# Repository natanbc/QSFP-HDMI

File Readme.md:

# QSFP to HDMI Breakout Boards

This repository contains two KiCad subprojects for the QSFP to HDMI breakout boards. These subprojects are designed to facilitate the conversion of QSFP signals to HDMI.

The concept has been created to be used on the Microsoft Stratix V FPGA accelerator card "Storey Peak". Jan Marjanovic has created a series of posts about the analysis of the card:

- [Part 1](https://j-marjanovic.io/stratix-v-accelerator-card-from-ebay.html)
- [Part 2](https://j-marjanovic.io/stratix-v-accelerator-card-from-ebay-part-2.html)
- [Part 3](https://j-marjanovic.io/stratix-v-accelerator-card-from-ebay-part-3.html)
- [Part 4](https://j-marjanovic.io/stratix-v-accelerator-card-from-ebay-part-4.html)
- [Part 5](https://j-marjanovic.io/stratix-v-accelerator-card-from-ebay-part-5.html)
- [Part 6](https://j-marjanovic.io/stratix-v-accelerator-card-from-ebay-part-6.html)
- [Part 7](https://j-marjanovic.io/stratix-v-accelerator-card-from-ebay-part-7.html)
- [Part 8](https://j-marjanovic.io/stratix-v-accelerator-card-from-ebay-part-8.html)

## Subprojects

### 1. QSFP breakout board

The project is just a breakout board for the QSFP connector allowing connection to the QSFP on the FPGA board.

### 2. QSFP to HDMI and UART Adapter

This subproject focuses on the design and implementation of an adapter that converts QSFP signals to HDMI. The key features include:

- QSFP connector for input signals
- HDMI connector for output signals
- USB-C connector for UART adapter

This board has been manufactured in JLCPCB, and has LCSC part numbers allowing assembly by them as well. Be sure to use 1mm PCBs to fit into the QSFP slot.

## Contributing

Contributions are welcome! Please fork the repository and submit a pull request with your improvements.

## License

This project is licensed under the MIT License. See the [LICENSE](LICENSE) file for details.

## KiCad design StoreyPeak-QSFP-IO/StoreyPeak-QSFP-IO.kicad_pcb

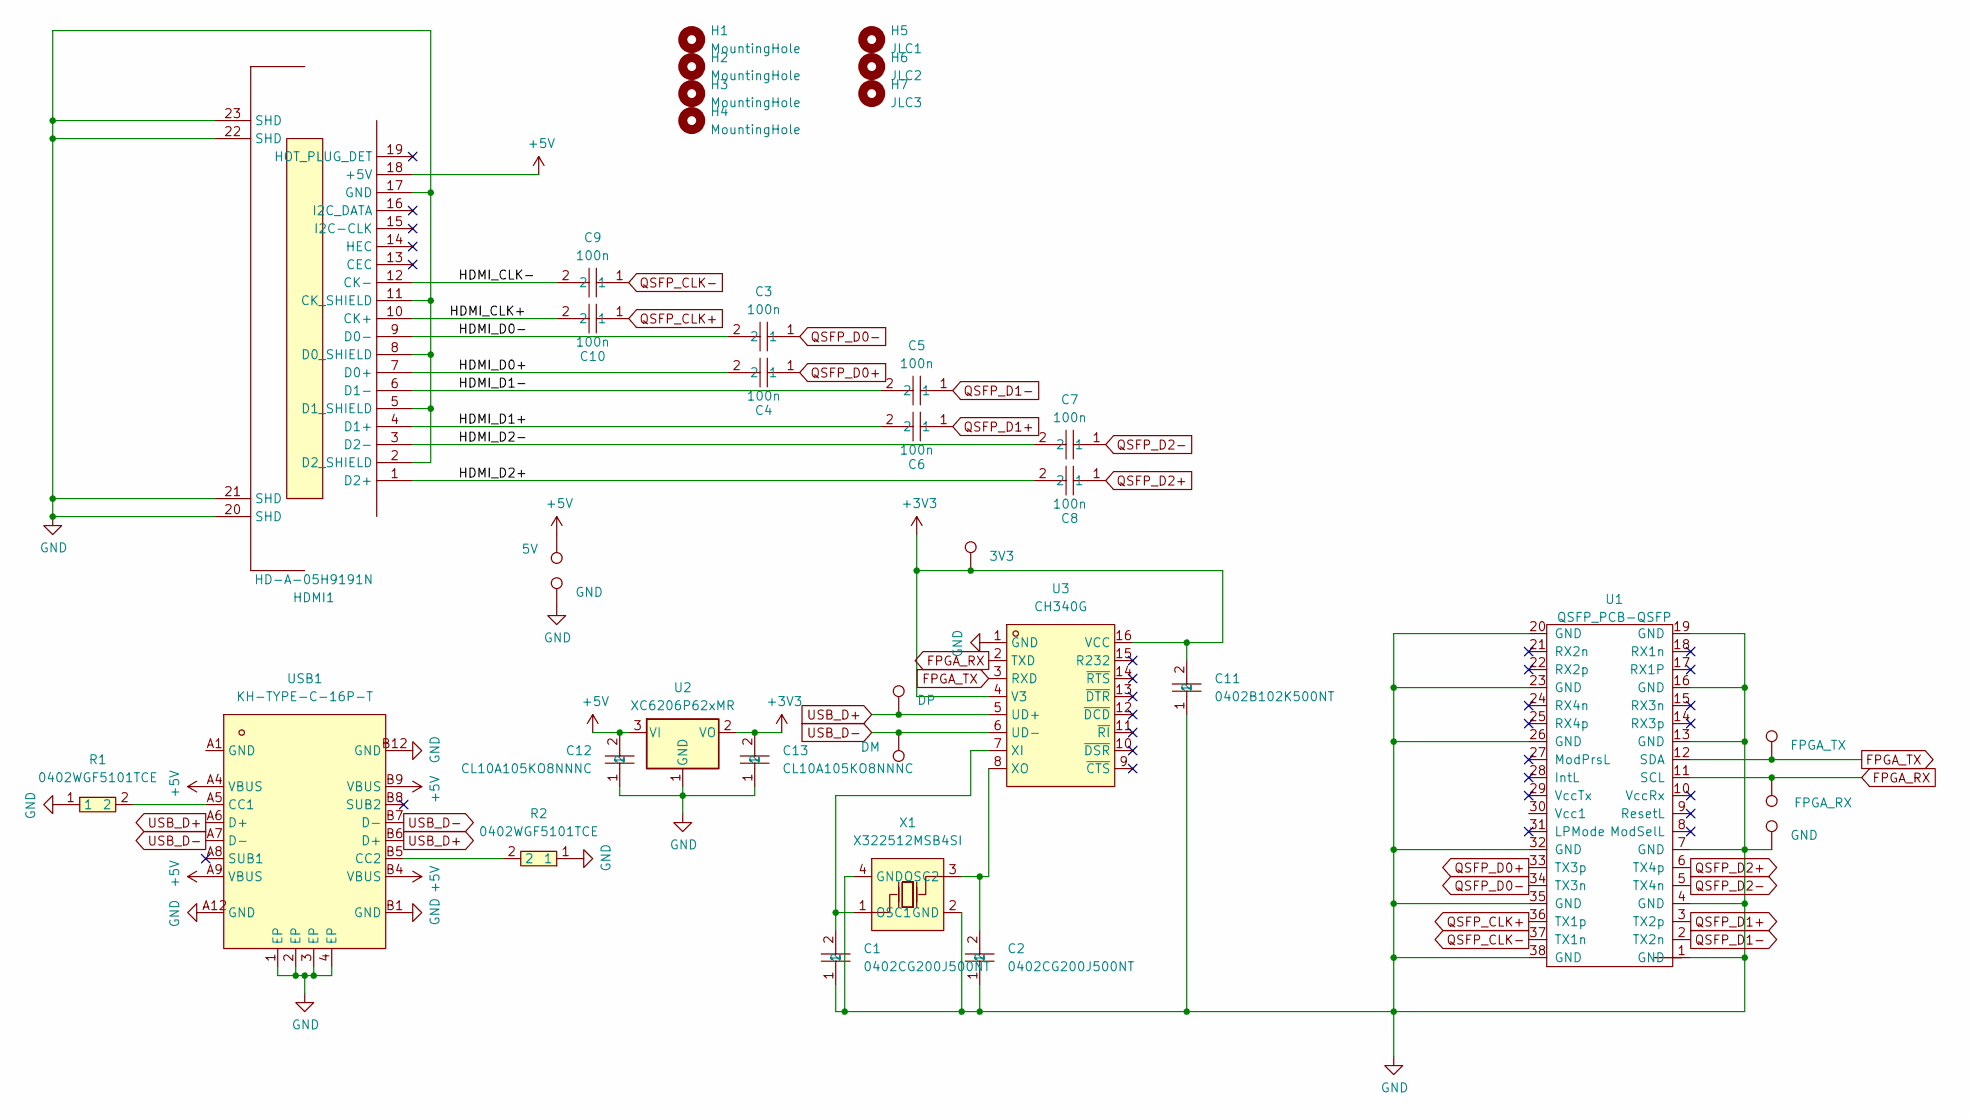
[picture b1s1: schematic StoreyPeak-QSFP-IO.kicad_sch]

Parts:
C1, C2: 0402CG200J500NT; C0402; LCSC Part C1554
C3, C4, C5, C6, C7, C8, C9, C10: 100n; C0402; LCSC Part C1525
C11: 0402B102K500NT; C0402; LCSC Part C1523
C12, C13: CL10A105KO8NNNC; C_0603_1608Metric; LCSC Part C1592
H1, H2, H3, H4: MountingHole; MountingHole_2.2mm_M2
H5: JLC1; JLCPCB_Tooling_Hole
H6: JLC2; JLCPCB_Tooling_Hole
H7: JLC3; JLCPCB_Tooling_Hole
HDMI1: HD-A-05H9191N; HDMI-SMD_HD-A-05H9192N; LCSC C18213861
R1, R2: 0402WGF5101TCE; R0402; LCSC Part C25905
TP1: 5V; TestPoint_Pad_1.5x1.5mm
TP2, TP7: GND; TestPoint_Pad_1.5x1.5mm
TP3: FPGA_RX; TestPoint_Pad_1.5x1.5mm
TP4: FPGA_TX; TestPoint_Pad_1.5x1.5mm
TP5: DP; TestPoint_Pad_1.5x1.5mm
TP6: DM; TestPoint_Pad_1.5x1.5mm
TP8: 3V3; TestPoint_Pad_1.5x1.5mm
U1: QSFP_PCB-QSFP; QSFP-Edge
U2: XC6206P62xMR; SOT-23-3; LCSC C2891841
U3: CH340G; SOIC-16_L9.9-W3.9-P1.27-LS6.0-BL; LCSC Part C14267
USB1: KH-TYPE-C-16P-T; USB-C-SMD_KH-TYPE-C-16P; LCSC Part C709358
X1: X322512MSB4SI; CRYSTAL-SMD_4P-L3.2-W2.5-BL; LCSC Part C9002

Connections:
+3V3: C11.2, C13.2, TP8.1, U2.2 (VO), U3.4 (V3), U3.16 (VCC); also elsewhere on the board
+5V: C12.2, HDMI1.18 (+5V), TP1.1, U2.3 (VI), USB1.A4 (VBUS), USB1.A9 (VBUS), USB1.B4 (VBUS), USB1.B9 (VBUS)
/HDMI_CLK+: C10.2, HDMI1.10 (CK+)
/HDMI_CLK-: C9.2, HDMI1.12 (CK-)
/HDMI_D0+: C4.2, HDMI1.7 (D0+)
/HDMI_D0-: C3.2, HDMI1.9 (D0-)
/HDMI_D1+: C6.2, HDMI1.4 (D1+)
/HDMI_D1-: C5.2, HDMI1.6 (D1-)
/HDMI_D2+: C8.2, HDMI1.1 (D2+)
/HDMI_D2-: C7.2, HDMI1.3 (D2-)
FPGA_RX: TP3.1, U1.11 (SCL), U3.2 (TXD)
FPGA_TX: TP4.1, U1.12 (SDA), U3.3 (RXD)
GND: C1.1, C2.1, C11.1, C12.1, C13.1, HDMI1.2 (D2_SHIELD), HDMI1.5 (D1_SHIELD), HDMI1.8 (D0_SHIELD), HDMI1.11 (CK_SHIELD), HDMI1.17 (GND), HDMI1.20 (SHD), HDMI1.21 (SHD), HDMI1.22 (SHD), HDMI1.23 (SHD), R1.1, R2.1, TP2.1, TP7.1, U1.1 (GND), U1.4 (GND), U1.7 (GND), U1.13 (GND), U1.16 (GND), U1.19 (GND), U1.20 (GND), U1.23 (GND), U1.26 (GND), U1.32 (GND), U1.35 (GND), U1.38 (GND), U2.1 (GND), U3.1 (GND), USB1.1 (EP), USB1.2 (EP), USB1.3 (EP), USB1.4 (EP), USB1.A12 (GND), USB1.B1 (GND), USB1.B12 (GND), X1.2 (GND), X1.4 (GND)
unnamed: C1.2, U3.7 (XI), X1.1 (OSC1)
unnamed: C2.2, U3.8 (XO), X1.3 (OSC2)
unnamed: R1.2, USB1.A5 (CC1)
unnamed: R2.2, USB1.B5 (CC2)
QSFP_CLK+: C10.1, U1.36 (TX1p)
QSFP_CLK-: C9.1, U1.37 (TX1n)
QSFP_D0+: C4.1, U1.33 (TX3p)
QSFP_D0-: C3.1, U1.34 (TX3n)
QSFP_D1+: C6.1, U1.3 (TX2p)
QSFP_D1-: C5.1, U1.2 (TX2n)
QSFP_D2+: C8.1, U1.6 (TX4p)
QSFP_D2-: C7.1, U1.5 (TX4n)
USB_D+: TP5.1, U3.5 (UD+), USB1.A6 (D+), USB1.B6 (D+)
USB_D-: TP6.1, U3.6 (UD-), USB1.A7 (D-), USB1.B7 (D-)

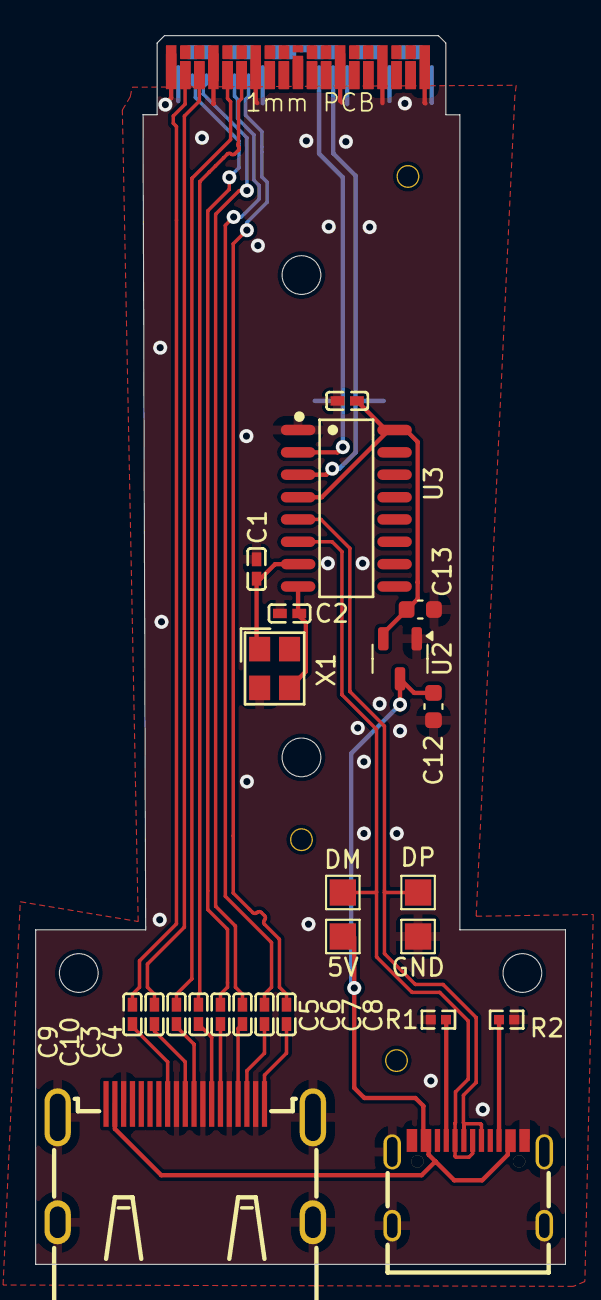
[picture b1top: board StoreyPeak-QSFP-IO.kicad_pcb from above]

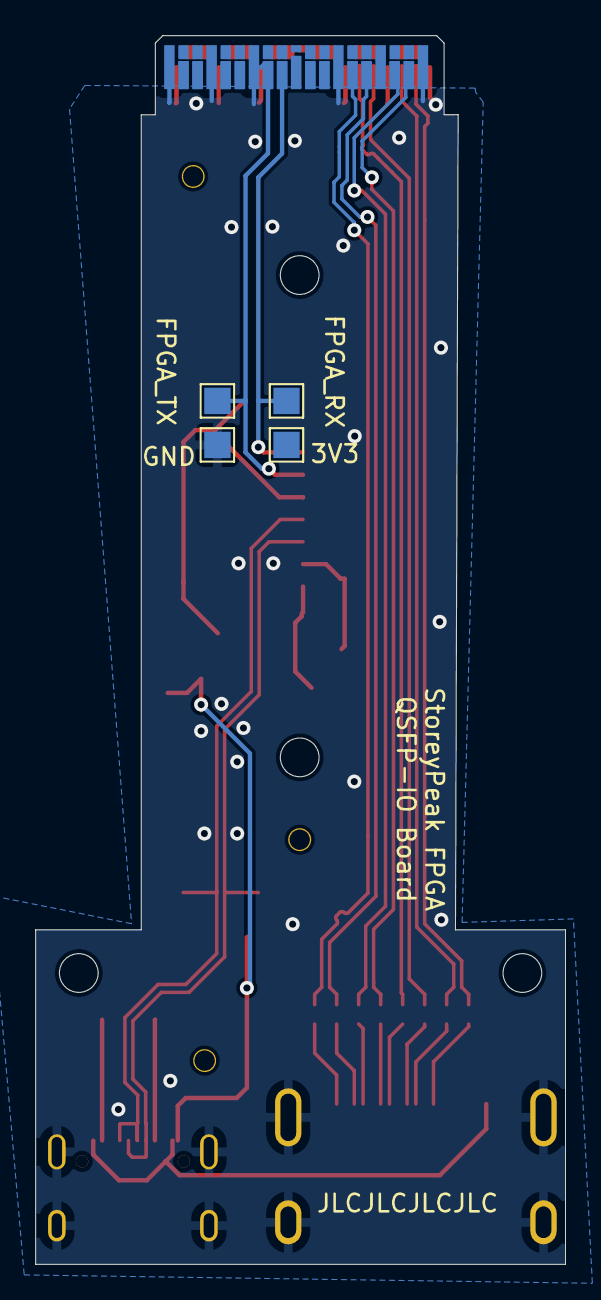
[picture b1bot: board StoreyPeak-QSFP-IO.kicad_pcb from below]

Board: 2 copper layers, 30.1 x 69.8 mm, 36 parts (4 on the bottom side), 27 nets.

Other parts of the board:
3V3: 3V3; TestPoint_Pad_1.5x1.5mm

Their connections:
+3V3: 3V3.1; also elsewhere on the board

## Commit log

2024-09-24 Initial import
2024-12-14 Use CH340G UART and USB-C port
2024-12-14 Use passives from JLCPCB basic library
2024-12-14 Use SMD crystal instead of THT
2024-12-14 Replace more passives with JLCPCB basic parts
2024-12-14 Add test points, add screw holes to schematic
2024-12-14 Fix board outline cuts
2024-12-15 Re-add vias (oops), add DP/DM pads, extend ground planes to cover entire board, stitch ground planes together
2024-12-15 Change board to 1mm
2024-12-15 Add DRC exclusions
2025-01-25 Change QSFP->HDMI mapping for better routing, skew match diffpairs
2025-01-25 Add GND pad next to UART pads, reroute 5V pad to avoid breaking GND plane below HDMI signals
2025-01-25 Remove backups folder
2025-01-25 Re-add accidentally deleted UART GND pad, move some traces to avoid cutting ground planes
2025-02-02 Add JLCPCB tooling holes
2025-02-02 Remove fp-info-cache
2025-03-01 Update README and images
2025-03-01 Increase clearance between USB-C port and HDMI port/CC resistors
2025-03-01 Warn about broken version
2025-03-01 Fix QSFP connector footprint (pins 1-19 were flipped)
2025-03-01 Fix board for right QSFP connector, change HDMI caps to 0402
2025-03-01 Update images, readme
2025-03-01 Increase clearance on USB pads for the casing
2025-03-16 Connect all USB-C GND pins to ground plane
2025-06-04 Hide part numbers that started showing after updating to KiCad 9
2025-06-09 Get 3.3V from LDO off USB port
2025-07-12 Connect HDMI ground pins
2025-07-12 Remove 3V3 text on back
2025-08-02 Fix wrong footprint for QSFP edge connector
2025-08-02 Readd 3V3 test point
2025-08-02 Fix flipped text on bottom silkscreen
